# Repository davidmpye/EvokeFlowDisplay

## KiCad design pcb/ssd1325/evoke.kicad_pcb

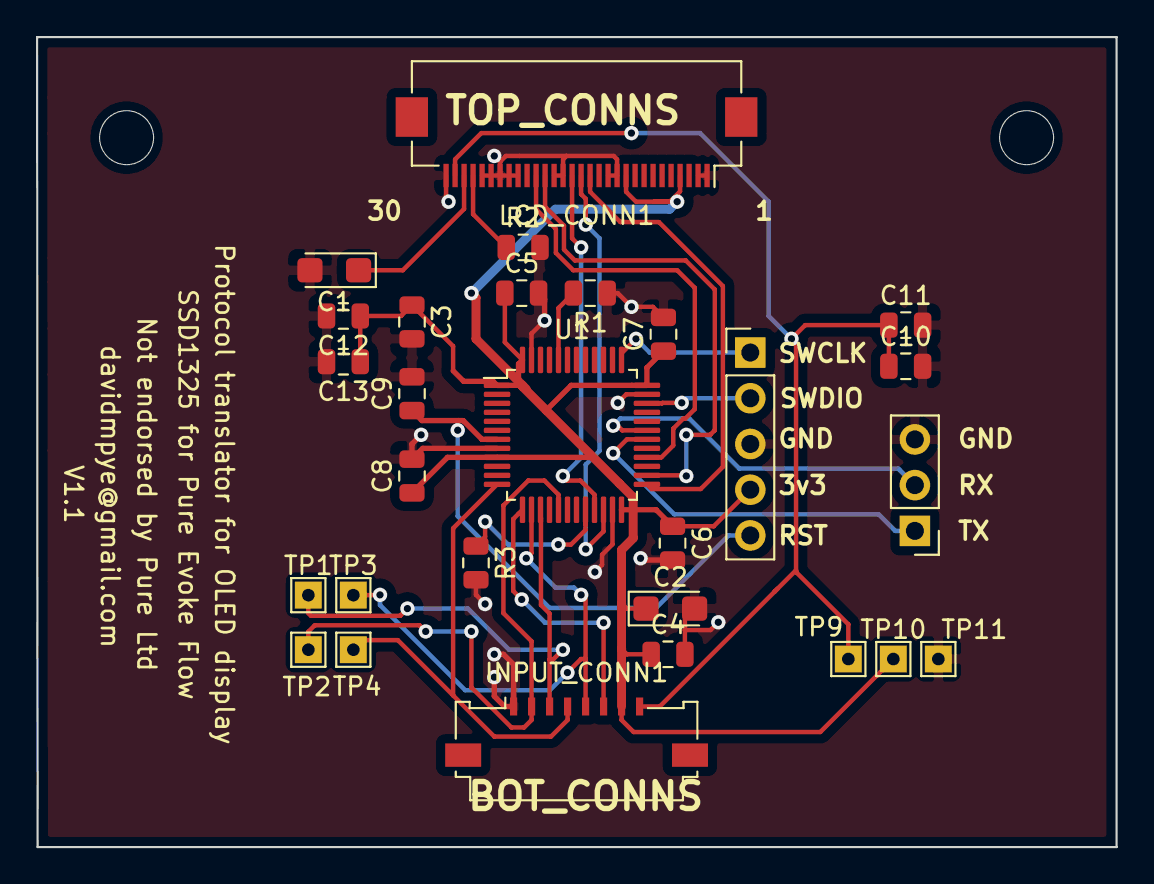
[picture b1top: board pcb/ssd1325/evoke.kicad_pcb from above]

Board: 2 copper layers, 60.0 x 45.0 mm, 28 parts (0 on the bottom side), 22 nets.

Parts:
C1: 4.7uF; CP_EIA-3216-18_Kemet-A
C2: 10uF; CP_EIA-3216-18_Kemet-A
C3, C4: C; C_0805_2012Metric
C5, C6, C7, C8, C9, C10, C12: 100nF; C_0805_2012Metric
C11: 10uF; C_0805_2012Metric
C13: 4.7uF; C_0805_2012Metric
INPUT_CONN1: CN101; Molex_200528-0080_1x08-1MP_P1.00mm_Horizontal
J1: Conn_01x03_Male; PinHeader_1x03_P2.54mm_Vertical
LCD_CONN1: Conn_01x30; Hirose_FH12-30S-0.5SH_1x30-1MP_P0.50mm_Horizontal
R1, R3: 10K; R_0805_2012Metric
R2: 1.2M; R_0805_2012Metric
ST_LINK1: Conn_01x05; PinHeader_1x05_P2.54mm_Vertical
TP1, TP2, TP3, TP4, TP9, TP10, TP11: TestPoint; TestPoint_THTPad_1.5x1.5mm_Drill0.7mm
U1: STM32F103C8Tx; LQFP-48_7x7mm_P0.5mm

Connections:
+3V3: C2.1, C3.1, C4.1, C5.1, C6.1, C7.1, C8.1, C12.1, C13.1, INPUT_CONN1.7, LCD_CONN1.4, LCD_CONN1.10, ST_LINK1.4, TP10.1, U1.1, U1.9, U1.24, U1.36, U1.48
CS_IN: INPUT_CONN1.5, TP3.1, U1.14
D_C_IN: INPUT_CONN1.4, TP4.1, U1.12
GND: C1.2, C2.2, C3.2, C4.2, C5.2, C6.2, C7.2, C8.2, C9.2, C10.2, C11.2, C12.2, C13.2, INPUT_CONN1.1, J1.3, LCD_CONN1.1, LCD_CONN1.2, LCD_CONN1.11, LCD_CONN1.12, LCD_CONN1.17, LCD_CONN1.18, LCD_CONN1.22, LCD_CONN1.23, LCD_CONN1.24, LCD_CONN1.25, LCD_CONN1.26, LCD_CONN1.30, R1.1, R2.2, R3.2, ST_LINK1.3, TP11.1, U1.8, U1.23, U1.35, U1.47
LCD_CS: LCD_CONN1.14, U1.25
LCD_DATA: LCD_CONN1.20, U1.28
LCD_D_C: LCD_CONN1.16, U1.21
LCD_RST: LCD_CONN1.15, U1.22
LCD_SCK: LCD_CONN1.19, U1.26
unnamed: C1.1, LCD_CONN1.28
unnamed: LCD_CONN1.27, R2.1
unnamed: R1.2, U1.44
unnamed: R3.1, U1.20
RESET: C9.1, ST_LINK1.5, U1.7
RST_IN: INPUT_CONN1.6, U1.13
SCK_IN: INPUT_CONN1.3, TP1.1, U1.15
SDIN_IN: INPUT_CONN1.2, TP2.1, U1.17
SWCLK: ST_LINK1.1, U1.37
SWDIO: ST_LINK1.2, U1.34
USART1_RX: J1.2, U1.31
USART1_TX: J1.1, U1.30
VCC: C10.1, C11.1, INPUT_CONN1.8, LCD_CONN1.29, TP9.1

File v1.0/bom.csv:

Comment,Designator,Footprint,LCSC, LCSC
"10uF","C1,C2","Capacitor_Tantalum_SMD:CP_EIA-3216-18_Kemet-A",""," C7171"
"C","C3,C4","Capacitor_SMD:C_0805_2012Metric","","C49678"
"100nF","C9,C5,C6,C7,C8,C10","Capacitor_SMD:C_0805_2012Metric","","C49678"
"CN101","INPUT_CONN1","Connector_FFC-FPC:Molex_200528-0080_1x08-1MP_P1.00mm_Horizontal",""
"Conn_01x30","LCD_CONN1","Connector_FFC-FPC:Hirose_FH12-30S-0.5SH_1x30-1MP_P0.50mm_Horizontal",""
"10K","R1,R3","Resistor_SMD:R_0805_2012Metric",""," C17414"
"1.5M","R2","Resistor_SMD:R_0805_2012Metric","","C26110"
"Conn_01x05","ST_LINK1","Connector_PinHeader_2.54mm:PinHeader_1x05_P2.54mm_Vertical",""
"STM32F103C8Tx","U1","Package_QFP:LQFP-48_7x7mm_P0.5mm","","C8734"

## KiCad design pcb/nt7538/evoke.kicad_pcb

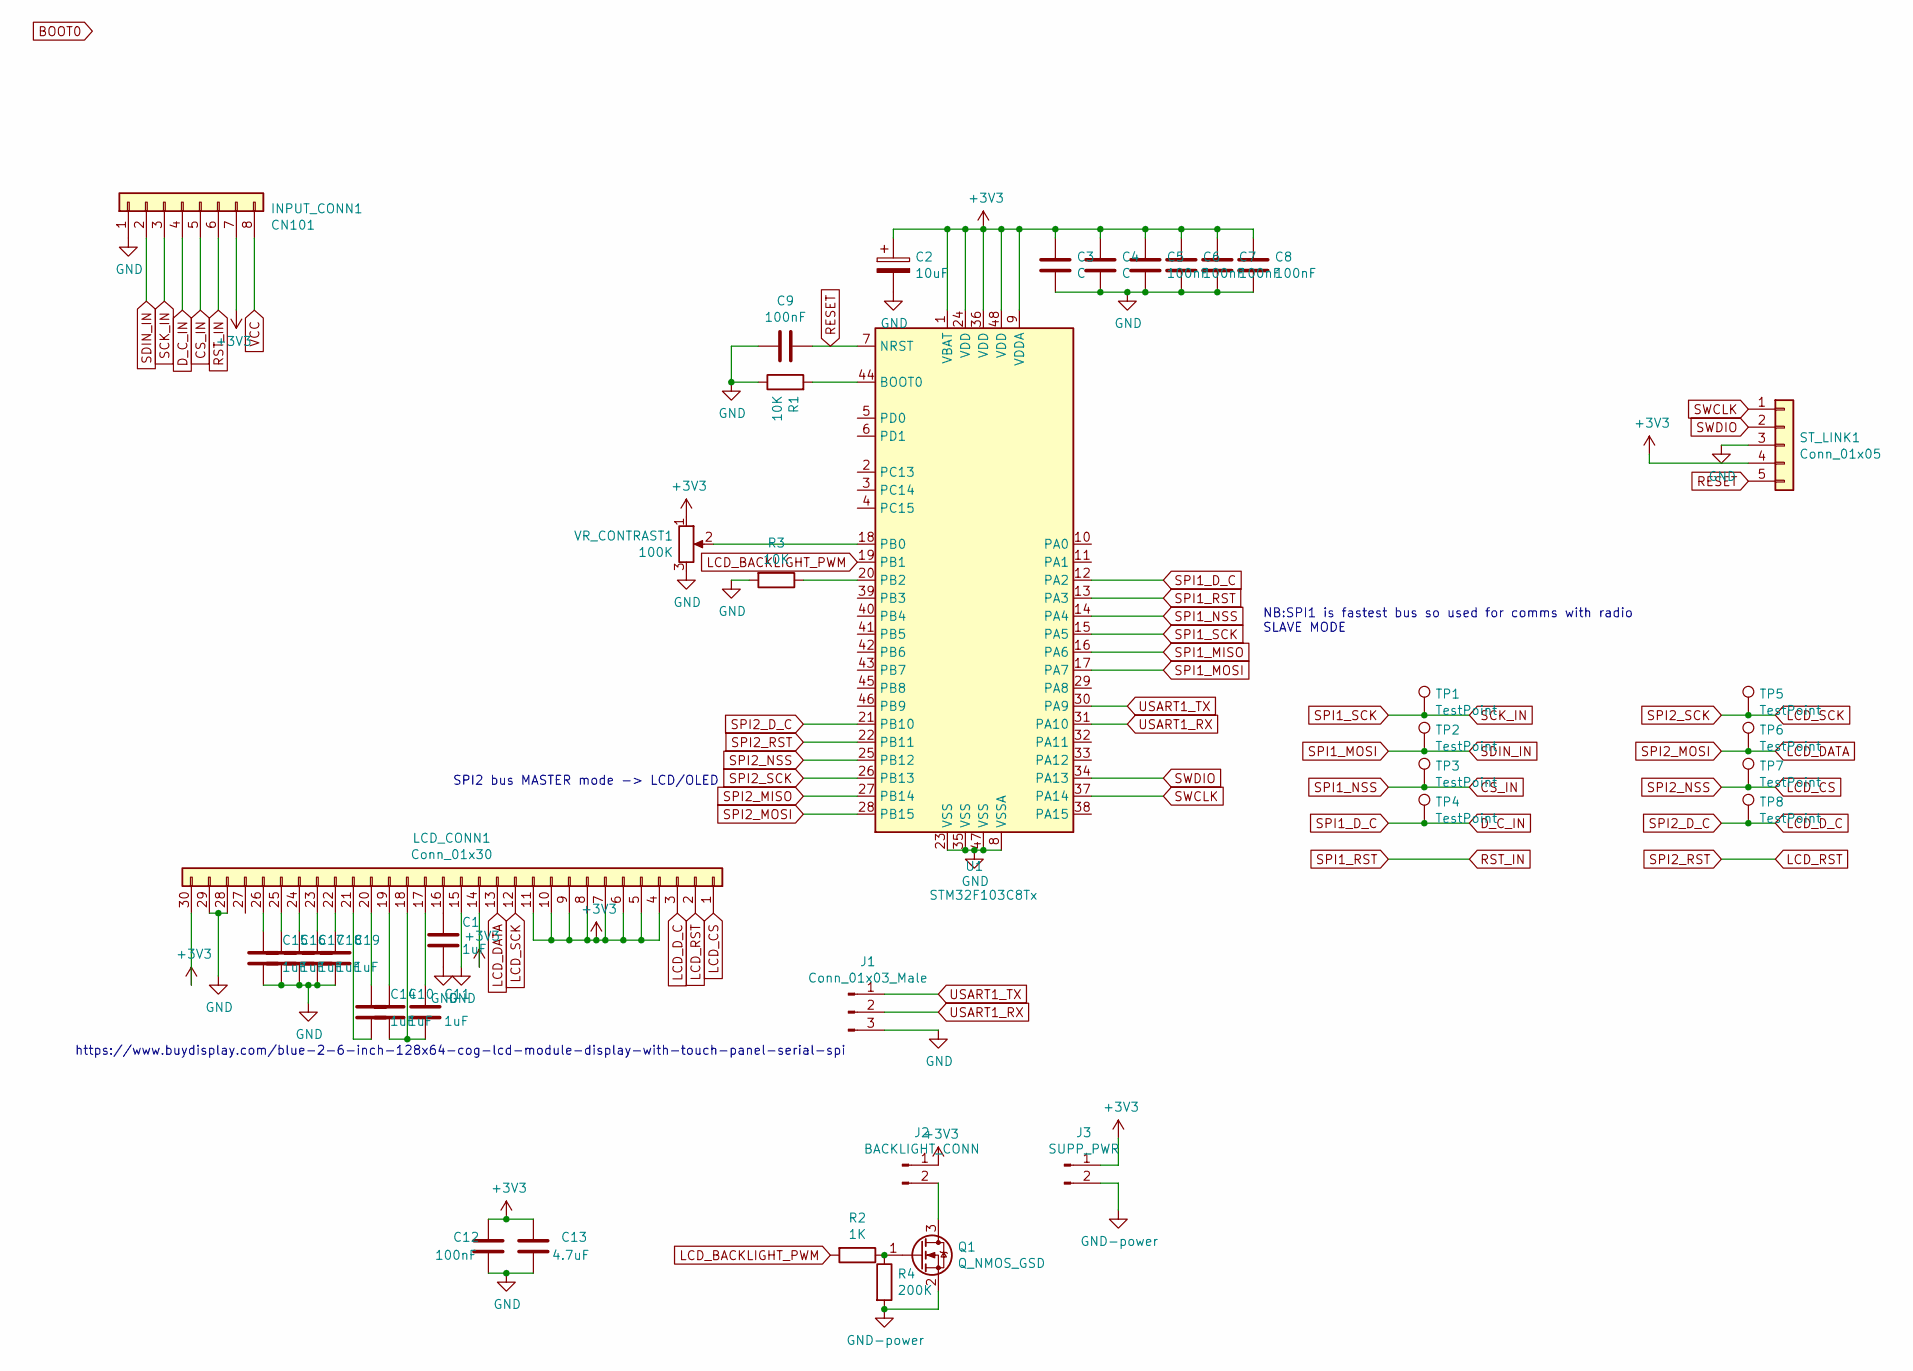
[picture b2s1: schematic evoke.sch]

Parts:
C1, C10, C11, C14, C15, C16, C17, C18, C19: 1uF; C_0805_2012Metric; LCSC C28323
C2: 10uF; CP_EIA-3216-18_Kemet-A; LCSC C7171
C3, C4: C; C_0805_2012Metric; LCSC C49678
C5, C6, C7, C8, C9, C12: 100nF; C_0805_2012Metric; LCSC C49678
C13: 4.7uF; C_0805_2012Metric; LCSC C1779
INPUT_CONN1: CN101; Molex_200528-0080_1x08-1MP_P1.00mm_Horizontal
J1: Conn_01x03_Male; PinHeader_1x03_P2.54mm_Vertical
J2: BACKLIGHT_CONN; JST_PH_S2B-PH-SM4-TB_1x02-1MP_P2.00mm_Horizontal
J3: SUPP_PWR; PinHeader_1x02_P2.54mm_Vertical
LCD_CONN1: Conn_01x30; Hirose_FH12-30S-0.5SH_1x30-1MP_P0.50mm_Horizontal
Q1: Q_NMOS_GSD; SOT-23; LCSC C347475
R1, R3: 10K; R_0805_2012Metric; LCSC C17414
R2: 1K; R_0805_2012Metric; LCSC C17513
R4: 200K; R_0805_2012Metric; LCSC C17539
ST_LINK1: Conn_01x05; PinHeader_1x05_P2.54mm_Vertical
TP1, TP2, TP3, TP4, TP5, TP6, TP7, TP8: TestPoint; TestPoint_Pad_D1.0mm
U1: STM32F103C8Tx; LQFP-48_7x7mm_P0.5mm; LCSC C8734
VR_CONTRAST1: 100K; Potentiometer_Vishay_T73YP_Vertical

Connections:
+3V3: C2.1, C3.1, C4.1, C5.1, C6.1, C7.1, C8.1, C12.1, C13.1, INPUT_CONN1.7, J2.1, J3.1, LCD_CONN1.4, LCD_CONN1.5, LCD_CONN1.6, LCD_CONN1.7, LCD_CONN1.8, LCD_CONN1.9, LCD_CONN1.10, LCD_CONN1.11, LCD_CONN1.14, LCD_CONN1.30, ST_LINK1.4, U1.1 (VBAT), U1.9 (VDDA), U1.24 (VDD), U1.36 (VDD), U1.48 (VDD), VR_CONTRAST1.1; also elsewhere on the board
CS_IN: INPUT_CONN1.5, TP3.1, U1.14 (PA4); also elsewhere on the board
D_C_IN: INPUT_CONN1.4, TP4.1, U1.12 (PA2); also elsewhere on the board
LCD_BACKLIGHT_PWM: R2.2, U1.19 (PB1)
LCD_CS: LCD_CONN1.1, TP7.1, U1.25 (PB12); also elsewhere on the board
LCD_DATA: LCD_CONN1.13, TP6.1, U1.28 (PB15); also elsewhere on the board
LCD_D_C: LCD_CONN1.3, TP8.1, U1.21 (PB10); also elsewhere on the board
LCD_RST: LCD_CONN1.2, U1.22 (PB11); also elsewhere on the board
LCD_SCK: LCD_CONN1.12, TP5.1, U1.26 (PB13); also elsewhere on the board
unnamed 9: C1.1, LCD_CONN1.16; also elsewhere on the board
unnamed 10: C10.1, LCD_CONN1.19; also elsewhere on the board
unnamed 11: C10.2, C11.2, LCD_CONN1.18; also elsewhere on the board
unnamed 12: C11.1, LCD_CONN1.17; also elsewhere on the board
unnamed 13: C14.1, LCD_CONN1.20; also elsewhere on the board
unnamed 14: C14.2, LCD_CONN1.21; also elsewhere on the board
unnamed 15: C15.1, LCD_CONN1.26; also elsewhere on the board
unnamed 16: C16.1, LCD_CONN1.25; also elsewhere on the board
unnamed 17: C17.1, LCD_CONN1.24; also elsewhere on the board
unnamed 18: C18.1, LCD_CONN1.23; also elsewhere on the board
unnamed 19: C19.1, LCD_CONN1.22; also elsewhere on the board
unnamed: J2.2, Q1.3 (D)
unnamed: Q1.1 (G), R2.1, R4.1
unnamed: R1.2, U1.44 (BOOT0)
unnamed: R3.1, U1.20 (PB2)
unnamed 32: U1.18 (PB0), VR_CONTRAST1.2; also elsewhere on the board
RESET: C9.1, ST_LINK1.5, U1.7 (NRST)
RST_IN: INPUT_CONN1.6, U1.13 (PA3); also elsewhere on the board
SCK_IN: INPUT_CONN1.3, TP1.1, U1.15 (PA5); also elsewhere on the board
SDIN_IN: INPUT_CONN1.2, TP2.1, U1.17 (PA7); also elsewhere on the board
SPI1_MISO: U1.16 (PA6)
SPI2_MISO: U1.27 (PB14)
SWCLK: ST_LINK1.1, U1.37 (PA14)
SWDIO: ST_LINK1.2, U1.34 (PA13)
USART1_RX: J1.2, U1.31 (PA10)
USART1_TX: J1.1, U1.30 (PA9)

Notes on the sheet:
NB:SPI1 is fastest bus so used for comms with radio SLAVE MODE
SPI2 bus MASTER mode -> LCD/OLED
https://www.buydisplay.com/blue-2-6-inch-128x64-cog-lcd-module-display-with-touch-panel-serial-spi

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
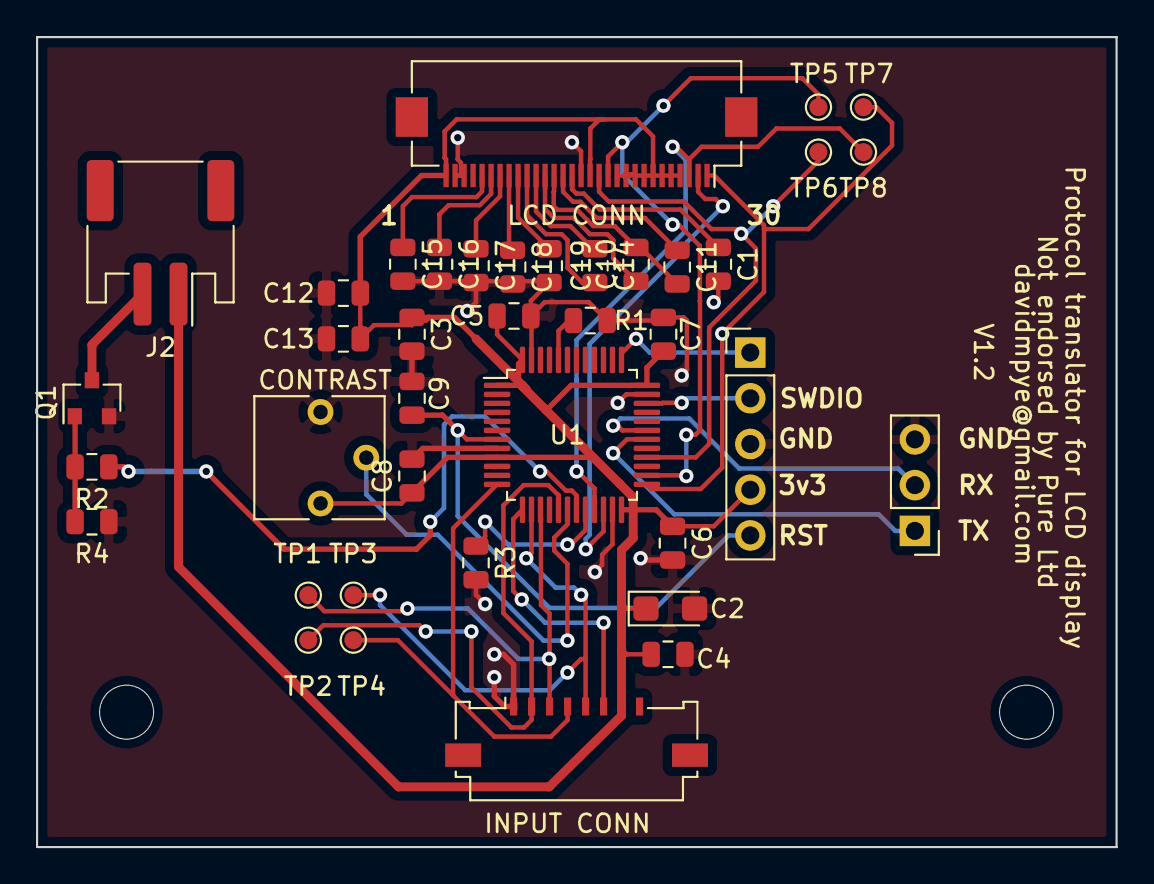
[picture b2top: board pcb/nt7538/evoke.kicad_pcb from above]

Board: 2 copper layers, 60.0 x 45.0 mm, 39 parts (0 on the bottom side), 34 nets.

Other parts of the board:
CONTRAST: 100K; Potentiometer_Vishay_T73YP_Vertical
INPUT CONN: CN101; Molex_200528-0080_1x08-1MP_P1.00mm_Horizontal
LCD CONN: Conn_01x30; Hirose_FH12-30S-0.5SH_1x30-1MP_P0.50mm_Horizontal

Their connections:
+3V3: CONTRAST.1, INPUT CONN.7, LCD CONN.4, LCD CONN.5, LCD CONN.6, LCD CONN.7, LCD CONN.8, LCD CONN.9, LCD CONN.10, LCD CONN.11, LCD CONN.14, LCD CONN.30; also elsewhere on the board
CS_IN: INPUT CONN.5; also elsewhere on the board
D_C_IN: INPUT CONN.4; also elsewhere on the board
LCD_CS: LCD CONN.1; also elsewhere on the board
LCD_DATA: LCD CONN.13; also elsewhere on the board
LCD_D_C: LCD CONN.3; also elsewhere on the board
LCD_RST: LCD CONN.2; also elsewhere on the board
LCD_SCK: LCD CONN.12; also elsewhere on the board
unnamed 9: LCD CONN.16; also elsewhere on the board
unnamed 10: LCD CONN.19; also elsewhere on the board
unnamed 11: LCD CONN.18; also elsewhere on the board
unnamed 12: LCD CONN.17; also elsewhere on the board
unnamed 13: LCD CONN.20; also elsewhere on the board
unnamed 14: LCD CONN.21; also elsewhere on the board
unnamed 15: LCD CONN.26; also elsewhere on the board
unnamed 16: LCD CONN.25; also elsewhere on the board
unnamed 17: LCD CONN.24; also elsewhere on the board
unnamed 18: LCD CONN.23; also elsewhere on the board
unnamed 19: LCD CONN.22; also elsewhere on the board
unnamed 32: CONTRAST.2; also elsewhere on the board
RST_IN: INPUT CONN.6; also elsewhere on the board
SCK_IN: INPUT CONN.3; also elsewhere on the board
SDIN_IN: INPUT CONN.2; also elsewhere on the board

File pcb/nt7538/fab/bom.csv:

Comment,Designator,Footprint,LCSC, LCSC
"1uF","C1,C10,C11,C14,C15,C16,C17,C18,C19","Capacitor_SMD:C_0805_2012Metric","","C28323"
"4.7uF","C13","Capacitor_SMD:C_0805_2012Metric","","C1779"
"10uF","C2","Capacitor_Tantalum_SMD:CP_EIA-3216-18_Kemet-A",""," C7171"
"C","C3,C4","Capacitor_SMD:C_0805_2012Metric","","C49678"
"100nF","C9,C5,C6,C7,C8,C12","Capacitor_SMD:C_0805_2012Metric","","C49678"
"CN101","INPUT_CONN1","Connector_FFC-FPC:Molex_200528-0080_1x08-1MP_P1.00mm_Horizontal",""
"Conn_01x03_Male","J1","Connector_PinHeader_2.54mm:PinHeader_1x03_P2.54mm_Vertical",""
"BACKLIGHT_CONN","J2","Connector_JST:JST_PH_S2B-PH-SM4-TB_1x02-1MP_P2.00mm_Horizontal",""
"SUPP_PWR","J3","Connector_PinHeader_2.54mm:PinHeader_1x02_P2.54mm_Vertical",""
"Conn_01x30","LCD_CONN1","Connector_FFC-FPC:Hirose_FH12-30S-0.5SH_1x30-1MP_P0.50mm_Horizontal",""
"Q_NMOS_GSD","Q1","Package_TO_SOT_SMD:SOT-23","","C347475"
"10K","R1,R3","Resistor_SMD:R_0805_2012Metric",""," C17414"
"1K","R2","Resistor_SMD:R_0805_2012Metric","","C17513"
"200K","R4","Resistor_SMD:R_0805_2012Metric","","C17539"
"Conn_01x05","ST_LINK1","Connector_PinHeader_2.54mm:PinHeader_1x05_P2.54mm_Vertical",""
"TestPoint","TP1,TP2,TP3,TP4,TP5,TP6,TP7,TP8","TestPoint:TestPoint_Pad_D1.0mm",""
"STM32F103C8Tx","U1","Package_QFP:LQFP-48_7x7mm_P0.5mm","","C8734"
"100K","VR_CONTRAST1","Potentiometer_THT:Potentiometer_Vishay_T73YP_Vertical",""

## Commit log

2020-05-01 Initial import of versioning
2020-05-01 Initial import of the python display 'driver'
2020-05-01 Import of v1.0 jlcpcb manufacture files
2020-05-01 Add gitignore
2020-05-01 Add initial import of code
2020-05-01 Add submodule
2020-05-01 Refactor the #VERTFLIP
2020-05-03 First attempt at restructuring!
2020-05-03 Further tweaks
2020-05-03 Typos/bugfixes
2020-05-03 Add GPL v3 licence and boilerplates
2020-05-03 LICENCE file addition, boilerplate
2020-05-03 Whitespace/comment formatting
2020-05-03 Squash compiler warnings (mostly by adding function prototypes etc)
2020-05-03 Rename uart_puts to usartPrint
2020-05-04 Initial trial of DMA (#define USE_DMA). Not working very well!
2020-05-04 Disabled by default
2020-05-05 Reinstate idle in main loop
2020-05-05 Only send updated pages to the display, rather than the whole FB.
2020-05-05 Refactoring of how commands work, as if you send commands from interrupt context, it mucks up the datablock that's being sent
2020-05-05 Fix the DMA priority problem, no glitches now
2020-05-05 Just send changed pages via DMA again
2020-05-05 Send the command block even in DMA mode
2020-05-05 Stop updating the display data if the screen is off
2020-05-06 Remove the USE_DMA define - it works so well, we'll just use DMA always!
2020-05-06 Documentation for the DMA pre/postamble
2020-05-11 Fix (I think!) for the screen corruption issue on tuning
2020-05-13 Tweak to address calculation
2020-05-19 Initial import for NT7538 driver LCD
2020-05-21 Add #define for init cmd length
2020-05-21 Add nt7538 object
2020-05-21 Move PCB into subdirectory to allow creation of LCD version
2020-05-21 Duplication of ssd1305 PCB design to NT7538 layout
2020-05-21 Add frame for NT7538 LCD from buydisplay.com https://www.buydisplay.com/white-2-6-inch-spi-serial-graphic-touch-screen-lcd-display-128x64-nt7538
2020-05-21 Initial draft of backlight PWM control
2020-05-25 Improve #defines to allow selecting display type and fix ND7538 spell error
2020-05-31 Initial changes for LCD support
2020-06-01 Further evolution of NT schmatic
2020-06-02 Fix bug with pins being wrong on connector, and add USART header
2020-06-02 Addition of additional components as per jack wan's schematic example
2020-06-02 Clarify 0xa4/0xa5 comments
2020-06-04 Put next revision into manufacture - hopefully ready to go, now with test points!
2020-06-04 Add fab for SSD1305
2020-06-16 Update code to use INTERNAL oscillator so it works without an external crystal
2020-06-20 Fix to use the same D_C pin as the GPIO on the board
2020-06-21 Commit of NT version including trimpot
2020-06-21 More NT7538 tweaks
2020-06-21 Move VCC comment to ssd1305.h
2020-06-22 NT7538 to manufacture
2020-06-22 Add fab files
2020-06-26 Initial add of instructions
2020-06-29 Addition of PWM backlight and contrast POT reading
2020-07-01 Move screw holes for the nt7538 PCB, and increment PCB version number to 1.1
2020-07-01 Add a #define to enable the contrast potentiometer (or not)
2020-07-04 Add OpenOCD lock files and adjust upload.sh to lock
2020-07-04 Backlight brightness off initially
2020-07-04 Fix - inital brightness to off
2020-07-07 Add final instructions
2020-07-16 Disable contrast pot by default
2020-07-16 Changes to make it upload and lock
2020-08-03 Change to cheaper (but still 25V rated) tantalum cap for C1
2020-08-15 Add LCD instructions
2020-08-15 add bom
2020-08-15 Updates to v1.2 for NT pcb - hole spacing redone
2020-08-15 Add second design of LCD frame
2020-08-15 Add lcd frames sliced gcode
2020-08-16 Tweak to make LCD aperture 0.25mm narrower so it grips more tightly
2020-08-17 Update instructions to use bracket clip
2020-08-17 Redo of bracketry
2020-08-23 Add pin notes for oasis flow
2020-08-30 Update instructions with warnings to not press too hard!
2020-09-06 Update to version 1.1 of OLED PCB with square THT TP pads
2020-09-06 Update LCD instructions
2020-10-25 Adjustments to allow adjustable contrast
2020-11-30 Fix cfgX
2020-12-07 Add comment for the horizontal flip option
2020-12-26 Add fix for 'not dimming enough' by changing the Phase 2 precharge time
2020-12-29 Add new mainbracket gcodes
2020-12-29 Removal of retaining clip - pointless
2021-04-20 change to gd32
2021-06-09 import of 'flipped' ssd1325 pcb
2021-06-11 Fix GD rotatoin
2021-06-22 Instructions for the SSD1325 version
2021-08-09 Add 'backwards' OLED25 slipsy
2021-08-10 Add the 25b instructions
2022-02-05 Add packing slip
2022-04-24 add f4 option
2022-04-24 add bracket for f4
2022-04-25 Add avanti trialbracket
2022-04-26 Updates for standoffs
2022-05-02 add avanti bracket parts
2022-05-02 Add sliced bits
2022-05-02 Change to 40% infill for printed parts
2022-07-04 Adjust hole and aperture size
2022-07-04 Add back the brim
2022-07-21 Change to the support material gap for easier separation
